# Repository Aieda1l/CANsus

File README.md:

# CANsus

**CANsus** ("CAN sustain") is an iterated CAN, power, and auxiliary-signal distribution PCB developed for **Newport Robotics Group (Team 948)**. The project evolved from a CAN-only terminal board into a compact, serviceable wiring hub with modular connectors, power distribution, status indication, and a documented hardware revision history.

## Project overview

Robot electrical systems accumulate many point-to-point connections that must remain reliable, easy to diagnose, and practical to service under time pressure. CANsus explores a purpose-built distribution board for organizing those connections in a repeatable PCB assembly instead of relying only on loose in-line wiring.

The available KiCad history spans **v10 through v16** and shows several major design iterations: connector-family changes, board-size optimization, addition of power and auxiliary signals, migration of support components to SMD footprints, and simplification of the final interface.

This repository is intended to show not only the final hardware, but also the engineering iteration behind it.

## Engineering highlights

- **Seven documented KiCad revisions (v10-v16)** compared from the supplied design files.
- Progressed from **CAN-only distribution** to a combined **CAN + 12 V/GND + auxiliary-signal** interface.
- Added **dual RJ45 interfaces**, a bulk capacitor, and an LED status circuit beginning in v13.
- Reworked the terminal architecture in v14 from many 2-position blocks to larger **WAGO 2601-series multi-position connectors**.
- Reduced the v14 board envelope from approximately **86 × 53 mm** to **73.25 × 52.94 mm** in v15 while removing one redundant auxiliary connector — about a **14.8% reduction in width**.
- v16 simplifies the auxiliary interface from four signal nets to **two signal nets**, repurposing the remaining terminal capacity for 12 V and GND.
- The v16 layout uses **1.5 mm routing for 12 V/GND distribution** and **0.25 mm routing for CAN and auxiliary signals**.
- Physical board photos and a mechanical render document the transition from PCB design to assembled hardware.

> Revision details below are reconstructed directly from differences in the supplied KiCad schematic and PCB files. Where the files do not record the reason for a change, the documentation describes only the observed design change rather than inventing a rationale.

## Latest supplied electrical architecture — v16

The v16 design is a 2-layer, nominal 1.6 mm PCB with an Edge.Cuts envelope of approximately **73.25 × 52.94 mm**.

| Interface | Function |
|---|---|
| J1-J4 | WAGO 2601-1104 CAN distribution blocks; repeated CAN_HI / CAN_LO connections |
| J5 | WAGO 2601-1104 carrying SIGNAL_1, SIGNAL_2, 12 V, and GND |
| J7 | WAGO 2601-1102 carrying 12 V and GND |
| RJ1, RJ2 | 12 V, GND, SIGNAL_1, SIGNAL_2, CAN_HI, and CAN_LO; pins 5/6 are intentionally unconnected in v16 |
| C1 | Bulk capacitance across 12 V and GND |
| D1 + R1 | Power/status LED circuit |
| H1, H2 | #4-40 mounting holes |

The v16 RJ45 mapping visible in the PCB source is:

| Pin | Signal |
|---:|---|
| 1 | 12 V |
| 2 | GND |
| 3 | SIGNAL_1 |
| 4 | SIGNAL_2 |
| 5 | NC |
| 6 | NC |
| 7 | CAN_HI |
| 8 | CAN_LO |

## Design evolution

| Revision | Key change |
|---|---|
| **v10** | CAN-only baseline using 18 WAGO 250-202 two-position terminals and four mounting holes. |
| **v11** | Switched to WAGO 2601-3102 connectors, reduced the terminal count to 12, and narrowed the board. |
| **v12** | Reduced the CAN terminal count again to 10 and substantially compacted the board outline. |
| **v13** | Major functional expansion: added 12 V/GND, SIGNAL_1-SIGNAL_4, two RJ45 connectors, bulk capacitance, and an LED/resistor indicator circuit. |
| **v14** | Major connector/mechanical redesign: moved to 2601-1104/1102 terminal blocks, changed RJ45 footprint family, migrated the LED/resistor support circuitry to SMD footprints, and reduced mounting holes from four to two. |
| **v15** | Removed one duplicated auxiliary terminal block and reduced board width from 86 mm to 73.25 mm. |
| **v16** | Simplified the auxiliary interface to SIGNAL_1/SIGNAL_2; RJ45 pins 5/6 became NC and J5 was repurposed to include 12 V/GND. |

See [REVISION_LOG.md](REVISION_LOG.md) for the source-derived comparison and dimensional details.

## Hardware

### Assembled board

The assembled-board photo shows multiple fabricated CANsus boards, lever terminals, modular connectors, the bulk capacitor, and an illuminated status LED.

### Mechanical / enclosure render

### Earlier board

The earlier photo visibly carries **CANsus Board v10** silkscreen. The photo filenames use a separate “Version 1 / Version 5” media-labeling scheme, so this repository treats the KiCad folder names (v10-v16) as the electrical design revision sequence.

## Repository contents

```text
.
├── LICENSE
├── README.md
├── REVISION_LOG.md
├── bom/
│   └── BOM.csv
├── docs/
│   ├── README.md
│   ├── cansus-board-layout.pdf
│   └── cansus-schematic.pdf
├── hardware/
│   └── kicad/
│       ├── CAN_board.kicad_pcb
│       ├── CAN_board.kicad_pro
│       ├── CAN_board.kicad_sch
│       ├── fp-lib-table
│       ├── sym-lib-table
│       └── README.md
└── photos/
    ├── cansus-v1.jpg
    ├── cansus-v5-assembled.jpg
    └── cansus-v5-render.jpg
```

## Reviewing the project

For a quick technical review:

1. Start with this README for the system architecture and design progression.
2. Read [REVISION_LOG.md](REVISION_LOG.md) for the v10-v16 hardware comparison.
3. Open the [KiCad source](hardware/kicad/) to inspect the schematic and routed PCB.
4. Review the [BOM](bom/BOM.csv) for component references.
5. Use the [PDF exports](docs/) and photos for a fast visual overview.

The browsable `hardware/kicad/` directory is the previously committed v15 source snapshot. The additional v10-v16 KiCad export set was used to reconstruct the revision history in this documentation. The supplied PDF exports also correspond to the four-signal v14/v15-era architecture; see [docs/README.md](docs/README.md).

## Tools and engineering scope represented

**KiCad 8 · schematic capture · PCB layout · connector/footprint selection · mixed through-hole/SMD design · mechanical packaging · hardware iteration · BOM/documentation · prototype assembly**

## Source notes

Some PCB 3D-model references use absolute paths from the original workstation, so a few models may be missing in KiCad's 3D viewer on another computer. The electrical schematic and PCB footprints are still embedded in the KiCad project files.

R1 is labeled simply `R` in the supplied schematic; its resistance value is therefore intentionally left unspecified in the BOM rather than guessed.

## License

Released under the [MIT License](LICENSE).

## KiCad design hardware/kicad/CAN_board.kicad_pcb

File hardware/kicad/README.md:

# KiCad source notes

The files in this directory are the **browsable v15 KiCad source snapshot** that was originally committed to the repository. A separate supplied export set containing v10-v16 was compared to build the source-derived [revision log](../../REVISION_LOG.md).

## Tool version

The supplied schematic and PCB files report **KiCad 8.0** generators.

## Files kept here

- `CAN_board.kicad_pro` — project settings
- `CAN_board.kicad_sch` — schematic
- `CAN_board.kicad_pcb` — PCB layout
- `fp-lib-table` — project footprint-library table
- `sym-lib-table` — project symbol-library table

Generated/local-state material such as `.history`, KiCad backups, `fp-info-cache`, and `.kicad_prl` is intentionally not committed.

## v15 snapshot architecture

This source snapshot contains:

- four 2601-1104 CAN distribution blocks (J1-J4)
- one 2601-1104 auxiliary block (J5) carrying SIGNAL_1-SIGNAL_4
- one 2601-1102 power block (J7) carrying 12 V/GND
- two RJ45 connectors carrying 12 V, GND, SIGNAL_1-SIGNAL_4, CAN_HI, and CAN_LO
- bulk capacitor C1
- 0603 LED D1
- 1206 resistor R1
- two #4-40 mounting holes

The later v16 export keeps the same board envelope and physical component count, but removes SIGNAL_3/SIGNAL_4 from the interface and repurposes part of J5 for 12 V/GND. See [REVISION_LOG.md](../../REVISION_LOG.md).

## Portability caveat

Some PCB 3D-model references point to absolute paths on the original designer's workstation, including local model paths for the RJ45, capacitor, and mechanical hardware. Those missing model paths do **not** change the copper or schematic source, but KiCad's 3D viewer may show missing models on another machine.

The schematic symbols and PCB footprints used by the design are embedded in the `.kicad_sch` and `.kicad_pcb` files, so the electrical/layout source remains inspectable even if an external library path is unavailable.

## Revision-label caveat

The historical folder names provide the most useful revision sequence. The PCB title blocks lag behind that sequence: v10-v13 carry a v10 title and v14-v16 carry a v14 title. The repository preserves the source as supplied rather than silently rewriting the title blocks.

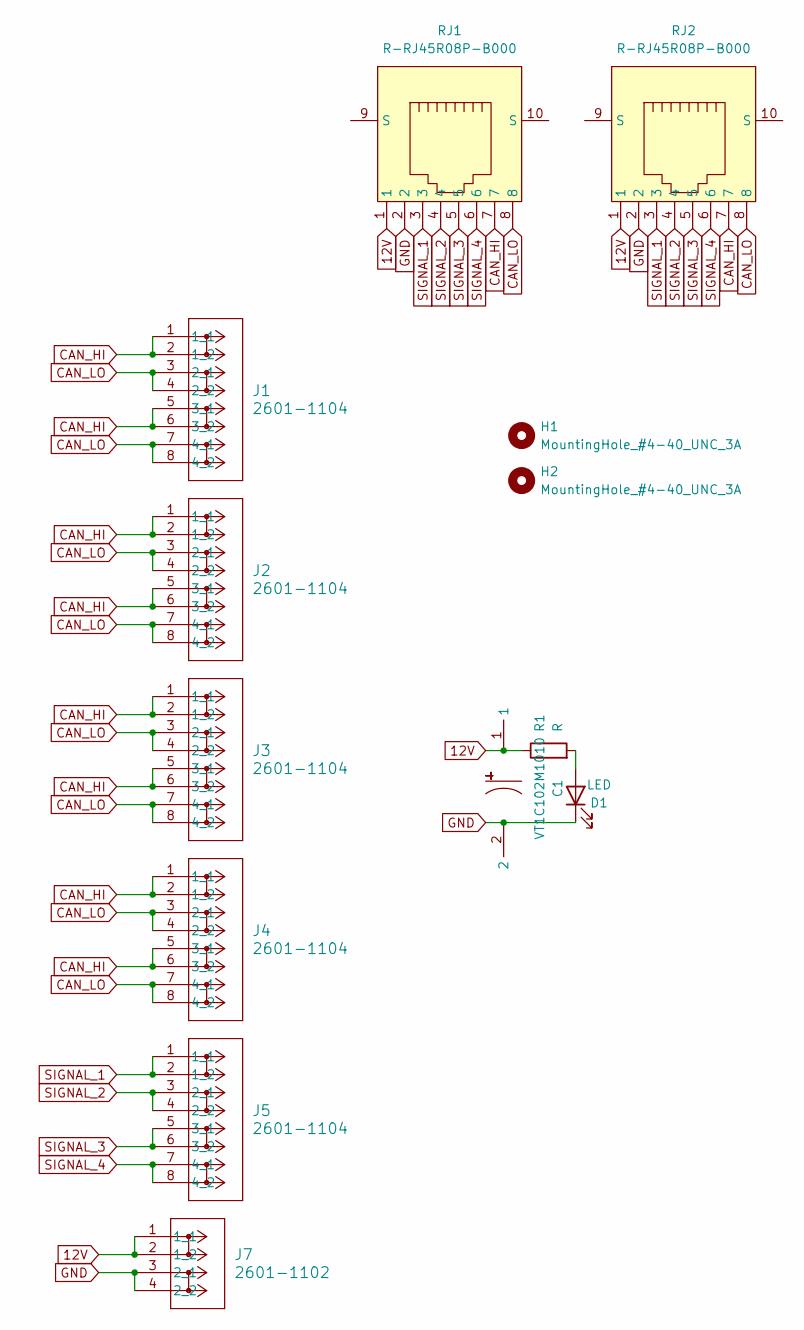
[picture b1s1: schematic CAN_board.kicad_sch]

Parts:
C1: VT1C102M1010; CAP-SMD_BD10.0-L10.3-W10.3-LS11.3-FD; LCSC Part C310843
D1: LED; LED_0603_1608Metric
H1, H2: MountingHole_#4-40_UNC_3A
J1, J2, J3, J4, J5: 2601-1104; CONN4_2601-1104_WAG
J7: 2601-1102; CONN2_2601-1102_WAG
R1: R; R_1206_3216Metric
RJ1, RJ2: R-RJ45R08P-B000; RJ45-TH_R-RJ45R08P-B000; LCSC Part C386756

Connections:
12V: C1.1, J7.1 (1_1), J7.2 (1_2), R1.1, RJ1.1, RJ2.1
CAN_HI: J1.1 (1_1), J1.2 (1_2), J1.5 (3_1), J1.6 (3_2), J2.1 (1_1), J2.2 (1_2), J2.5 (3_1), J2.6 (3_2), J3.1 (1_1), J3.2 (1_2), J3.5 (3_1), J3.6 (3_2), J4.1 (1_1), J4.2 (1_2), J4.5 (3_1), J4.6 (3_2), RJ1.7, RJ2.7
CAN_LO: J1.3 (2_1), J1.4 (2_2), J1.7 (4_1), J1.8 (4_2), J2.3 (2_1), J2.4 (2_2), J2.7 (4_1), J2.8 (4_2), J3.3 (2_1), J3.4 (2_2), J3.7 (4_1), J3.8 (4_2), J4.3 (2_1), J4.4 (2_2), J4.7 (4_1), J4.8 (4_2), RJ1.8, RJ2.8
GND: C1.2, D1.1 (K), J7.3 (2_1), J7.4 (2_2), RJ1.2, RJ2.2
unnamed: D1.2 (A), R1.2
SIGNAL_1: J5.1 (1_1), J5.2 (1_2), RJ1.3, RJ2.3
SIGNAL_2: J5.3 (2_1), J5.4 (2_2), RJ1.4, RJ2.4
SIGNAL_3: J5.5 (3_1), J5.6 (3_2), RJ1.5, RJ2.5
SIGNAL_4: J5.7 (4_1), J5.8 (4_2), RJ1.6, RJ2.6

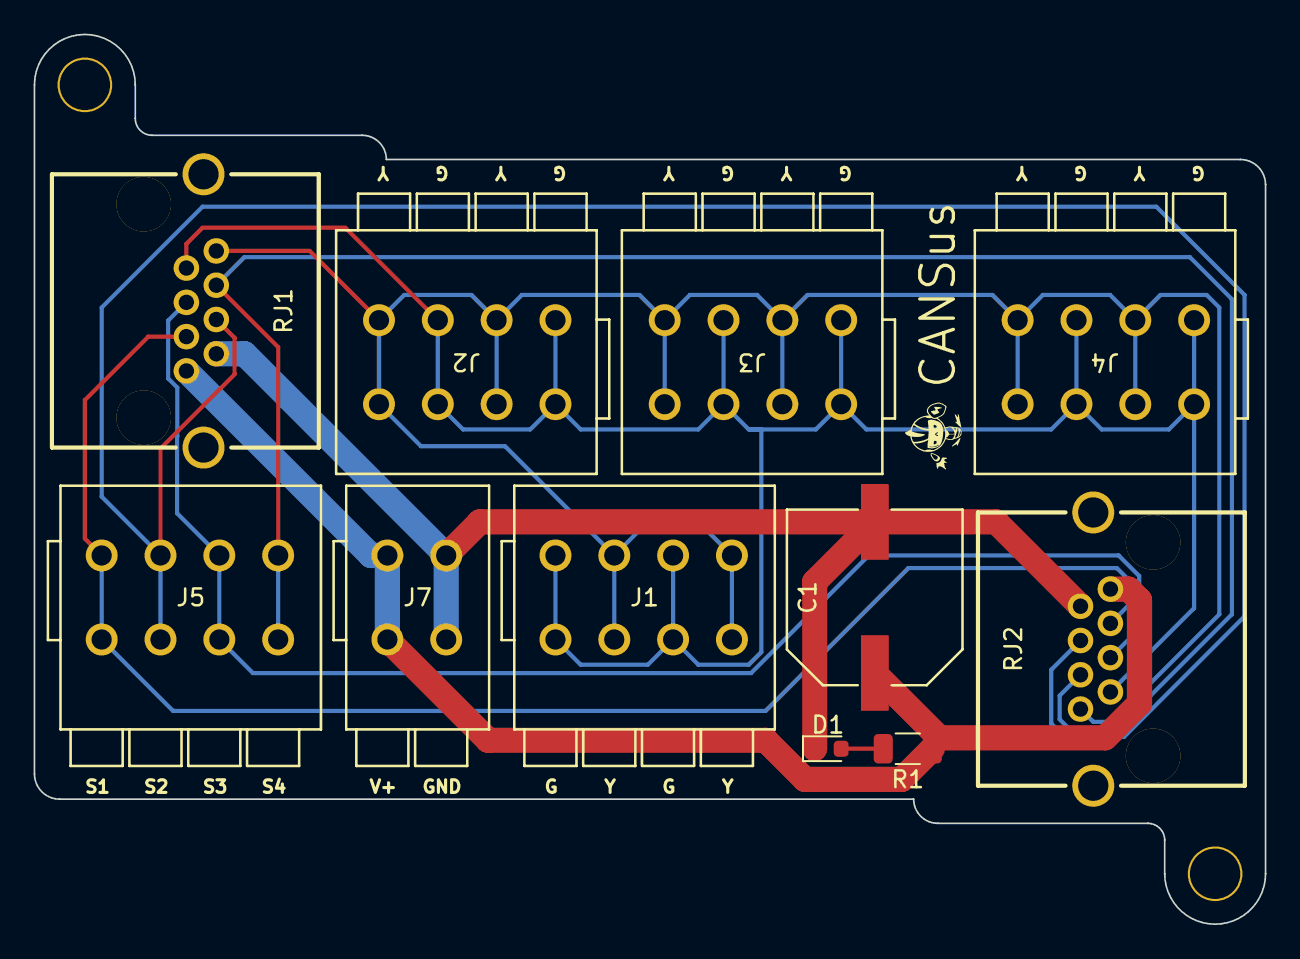
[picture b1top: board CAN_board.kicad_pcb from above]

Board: 2 copper layers, 73.2 x 52.9 mm, 13 parts (0 on the bottom side), 9 nets.
